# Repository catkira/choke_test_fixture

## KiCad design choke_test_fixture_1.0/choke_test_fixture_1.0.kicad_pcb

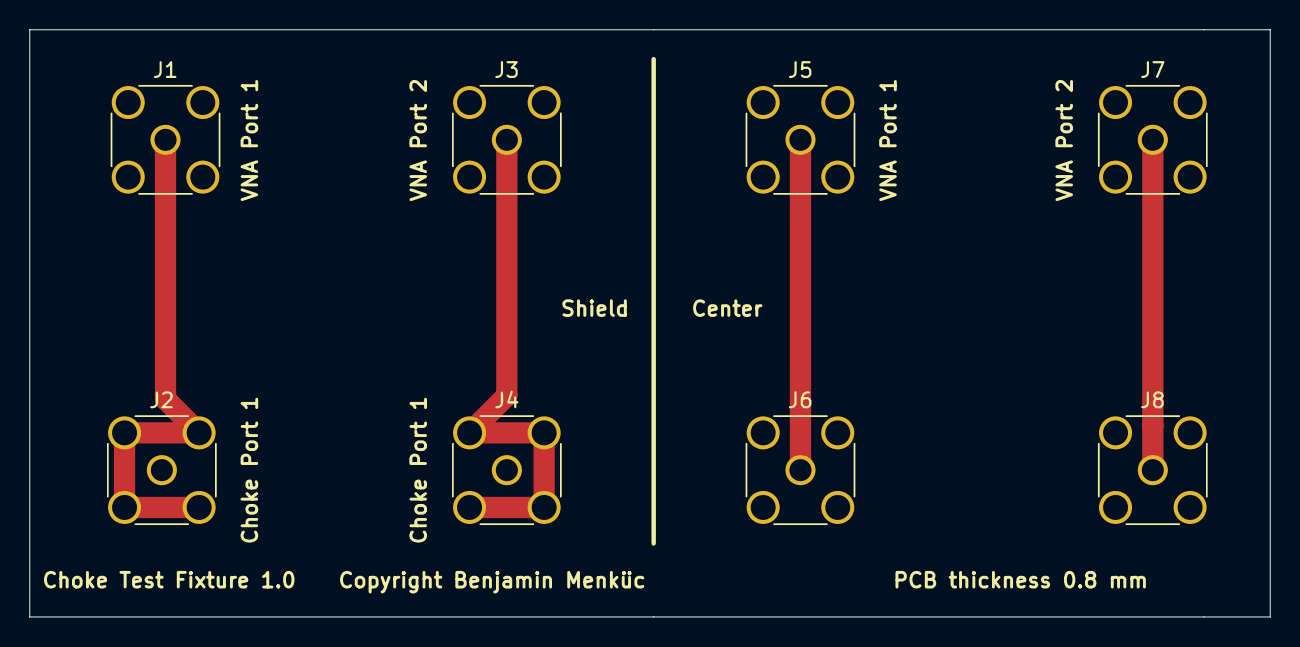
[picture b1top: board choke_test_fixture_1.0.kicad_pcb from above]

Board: 2 copper layers, 84.5 x 40.0 mm, 8 parts (0 on the bottom side), 5 nets.

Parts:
J1, J5: VNA_Port1; SMA_Amphenol_132134_Vertical
J2, J6: Choke_Port1; SMA_Amphenol_132134_Vertical
J3, J7: VNA_Port2; SMA_Amphenol_132134_Vertical
J4, J8: Choke_Port2; SMA_Amphenol_132134_Vertical

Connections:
GND: J1.2, J3.2, J5.2, J7.2
unnamed: J1.1, J2.2
unnamed: J3.1, J4.2
unnamed: J5.1, J6.1
unnamed: J7.1, J8.1

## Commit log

2020-07-16 Version 1.0 completed
2020-07-17 corrected copper fill

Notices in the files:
choke_test_fixture_1.0/choke_test_fixture_1.0.kicad_pcb:
Copyright Benjamin Menküc
